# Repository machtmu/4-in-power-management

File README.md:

# 4 Inch Power Management Subsystem
I'm not gonna lie, this was a beast  

As part of the SPRINT ecosystem with MACH, this board was deisgned in the span of 5 days (From architecture to schematic to layout to production). These were not a good 5 days   

## Functionality
4 Cell BMS with high side protection FETs, integrated NVDC charging for up to 5A @ battery voltage, 3 power rails, 5V, 3.3V @ ~3A, 24V @1.8A (Shoutout Tristan)   
BMS supports up to ~5.7A due to the FET's, but if re speced, could probably go higher   
XT30's as output for 24V, input for charger and input for battery   
JST XH as input for cell balacing   
 Low side current sensing for OCP detection (or wtv else you need current for)  
 ## TODO:  
 I should change that load resistor but lowkey too tired rn :wilted_rose:   
 Order it lmao  
# Authors:  
 Architecture: javezki  
 BMS, 5V 3.3V: javezki  
 Charger, 24V Boost: kayessi 
 Layout: javezki
---

<div align="center">
  <div>

    <p><em>3D Render</em></p>
  </div>
  <br>

  <div>
    <br>
    <p><em>Schematic</em></p>
  </div>
  <br>
  
  <div>
    
    <br>
    <em>Footprint</em>
  </div>
</div>

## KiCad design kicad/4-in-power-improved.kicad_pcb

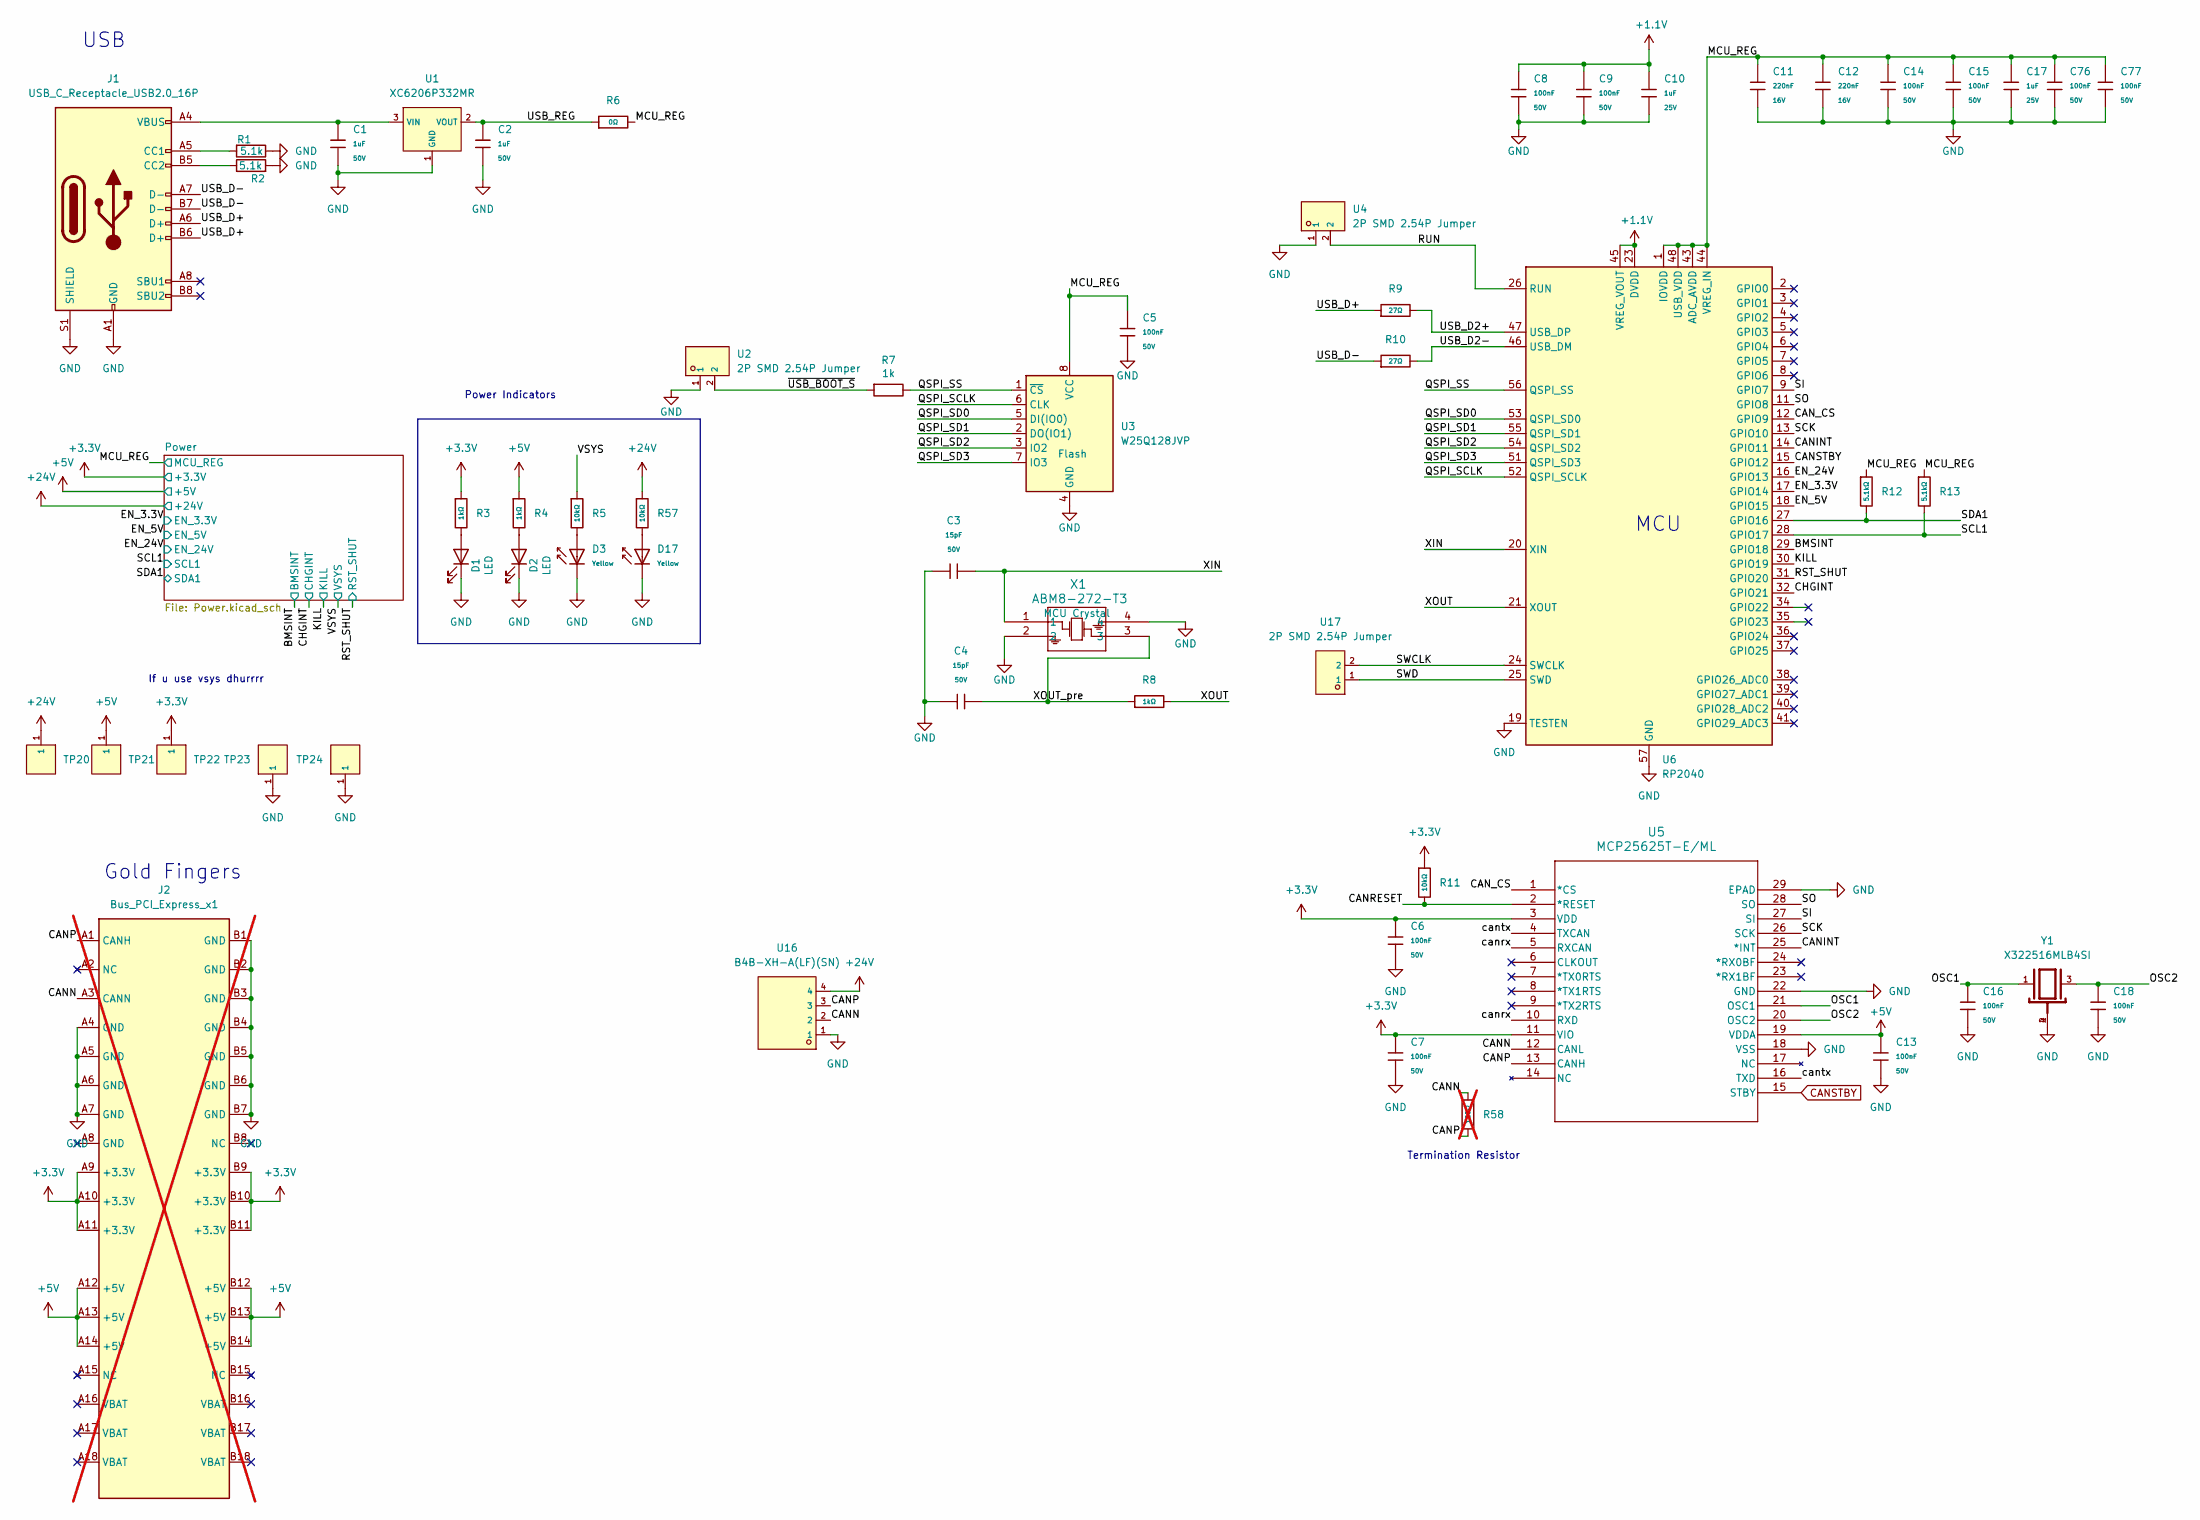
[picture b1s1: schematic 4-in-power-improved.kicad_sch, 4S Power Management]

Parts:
C1, C2: 1uF; C_0603; Voltage Rated 50V; Tolerance ±10%; Part CL10A105KB8NNNC; LCSC C15849
C3, C4: 15pF; C_0402; Voltage Rated 50V; Tolerance ±5%; Part 0402CG150J500NT; LCSC C1548
C5, C6, C7, C8, C9, C13, C14, C15, C16, C18, C76, C77: 100nF; C_0402; Voltage Rated 50V; Tolerance ±10%; Part CL05B104KB54PNC; LCSC C307331
C10, C17: 1uF; C_0402; Voltage Rated 25V; Tolerance ±10%; Part CL05A105KA5NQNC; LCSC C52923
C11, C12: 220nF; C_0402; Voltage Rated 16V; Tolerance ±10%; Part CL05B224KO5NNNC; LCSC C16772
D1, D2: LED; LED_0603_1608Metric; LCSC PN C2286
D3, D17: Yellow; D_0603; Forward Voltage (VF) 1.6V~2.6V; Part NCD0603Y2; LCSC C89811
J1: USB_C_Receptacle_USB2.0_16P; USB_C_Receptacle_Palconn_UTC16-G; LCSC PN C2765186
J2: Bus_PCI_Express_x1; PCIeX1; not fitted
R1, R2: 5.1k; R_0402_1005Metric; LCSC PN C25905
R3, R4, R8: 1kΩ; R_0402; Overload Voltage (Max) 50V; Tolerance ±1%; Part 0402WGF1001TCE; LCSC C11702
R5, R11, R57: 10kΩ; R_0402; Overload Voltage (Max) 50V; Tolerance ±1%; Part 0402WGF1002TCE; LCSC C25744
R6: 0Ω; R_0603; Overload Voltage (Max) 75V; Tolerance ±1%; Part 0603WAF0000T5E; LCSC C21189
R7: 1k; R_0402_1005Metric; LCSC Part # C11702
R9, R10: 27Ω; R_0603; Overload Voltage (Max) 75V; Tolerance ±1%; Part 0603WAF270JT5E; LCSC C25190
R12, R13: 5.1kΩ; R_0402; Overload Voltage (Max) 50V; Tolerance ±1%; Part 0402WGF5101TCE; LCSC C25905
R58: 120Ω; R_1206; Overload Voltage (Max) 200V; Tolerance ±1%; Part 1206W4F1200T5E; LCSC C17909; not fitted
TP20, TP21, TP22, TP23, TP24: RH-5015; SMD_RH-5015; LCSC C5199798
U1: XC6206P332MR; SOT-23-3_L2.9-W1.6-P1.90-LS2.8-BR; Output Voltage 3.3V; Dropout Voltage 680mV@(100mA); Part XC6206P332MR-G; LCSC C5446
U2, U4, U17: 2P SMD 2.54P Jumper; HDR-SMD_2P-P2.54-V-M-S4.8_DZ254S-11-02-50; LCSC C17702633
U3: W25Q128JVP; WSON-8-1EP_6x5mm_P1.27mm_EP3.4x4.3mm; LCSC C190862
U5: MCP25625T-E/ML; QFN-28_L6.0-W6.0-P0.65-BL-EP3.7; LCSC Part # C191253
U6: RP2040; QFN-56-1EP_7x7mm_P0.4mm_EP3.2x3.2mm; LCSC C2040
U16: B4B-XH-A(LF)(SN); CONN-TH_B4B-XH-A-LF-SN; LCSC C144395
X1: ABM8-272-T3; CRYSTAL-SMD_4P-L3.2-W2.5-BL; LCSC Part # C20625731
Y1: X322516MLB4SI; CRYSTAL-SMD_4P-L3.2-W2.5-BL; PARTREV N/A; LCSC Part # C12668

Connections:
+1.1V: C8.1, C9.1, C10.1, U6.23 (DVDD), U6.45 (VREG_VOUT), U6.50 (DVDD)
+3.3V: C6.1, C7.1, J2.A9 (+3.3V), J2.A10 (+3.3V), J2.A11 (+3.3V), J2.B9 (+3.3V), J2.B10 (+3.3V), J2.B11 (+3.3V), R3.1, R11.1, TP22.1, U5.3 (VDD), U5.11 (VIO); also elsewhere on the board
+5V: C13.1, J2.A12 (+5V), J2.A13 (+5V), J2.A14 (+5V), J2.B12 (+5V), J2.B13 (+5V), J2.B14 (+5V), R4.1, TP21.1, U5.19 (VDDA); also elsewhere on the board
+24V: R57.1, TP20.1, U16.4; also elsewhere on the board
/BMSINT: U6.29 (GPIO18); also elsewhere on the board
/CANINT: U5.25 (*INT), U6.14 (GPIO11)
/CANN: J2.A3 (CANN), R58.1, U5.12 (CANL), U16.2
/CANP: J2.A1 (CANH), R58.2, U5.13 (CANH), U16.3
/CANRESET: R11.2, U5.2 (*RESET)
/CAN_CS: U5.1 (*CS), U6.12 (GPIO9)
/CHGINT: U6.32 (GPIO21); also elsewhere on the board
/EN_3.3V: U6.17 (GPIO14); also elsewhere on the board
/EN_5V: U6.18 (GPIO15); also elsewhere on the board
/EN_24V: U6.16 (GPIO13); also elsewhere on the board
/KILL: U6.30 (GPIO19); also elsewhere on the board
/MCU_REG: C5.1, C11.1, C12.1, C14.1, C15.1, C17.1, C76.1, C77.1, R6.2, R12.1, R13.1, U3.8 (VCC), U6.1 (IOVDD), U6.10 (IOVDD), U6.22 (IOVDD), U6.33 (IOVDD), U6.42 (IOVDD), U6.43 (ADC_AVDD), U6.44 (VREG_IN), U6.48 (USB_VDD), U6.49 (IOVDD); also elsewhere on the board
/OSC1: C16.1, U5.21 (OSC1), Y1.1
/OSC2: C18.1, U5.20 (OSC2), Y1.3
/QSPI_SCLK: U3.6 (CLK), U6.52 (QSPI_SCLK)
/QSPI_SD0: U3.5 (DI(IO0)), U6.53 (QSPI_SD0)
/QSPI_SD1: U3.2 (DO(IO1)), U6.55 (QSPI_SD1)
/QSPI_SD2: U3.3 (IO2), U6.54 (QSPI_SD2)
/QSPI_SD3: U3.7 (IO3), U6.51 (QSPI_SD3)
/QSPI_SS: R7.1, U3.1 (~CS), U6.56 (QSPI_SS)
/RST_SHUT: U6.31 (GPIO20); also elsewhere on the board
/RUN: U4.2, U6.26 (RUN)
/SCK: U5.26 (SCK), U6.13 (GPIO10)
/SCL1: R13.2, U6.28 (GPIO17); also elsewhere on the board
/SDA1: R12.2, U6.27 (GPIO16); also elsewhere on the board
/SI: U5.27 (SI), U6.9 (GPIO7)
/SO: U5.28 (SO), U6.11 (GPIO8)
/SWCLK: U6.24 (SWCLK), U17.2
/SWD: U6.25 (SWD), U17.1
/USB_D2+: R9.2, U6.47 (USB_DP)
/USB_D2-: R10.2, U6.46 (USB_DM)
/USB_D+: J1.A6 (D+), J1.B6 (D+), R9.1
/USB_D-: J1.A7 (D-), J1.B7 (D-), R10.1
/USB_REG: C2.1, R6.1, U1.2 (VOUT)
/VSYS: R5.1; also elsewhere on the board
/XIN: C3.2, U6.20 (XIN), X1.1
/XOUT: R8.2, U6.21 (XOUT)
/XOUT_pre: C4.2, R8.1, X1.3
/canrx: U5.5 (RXCAN), U5.10 (RXD)
/cantx: U5.4 (TXCAN), U5.16 (TXD)
/~USB_BOOT_S: R7.2, U2.2
CANSTBY: U5.15 (STBY), U6.15 (GPIO12)
GND: C1.2, C2.2, C3.1, C4.1, C5.2, C6.2, C7.2, C8.2, C9.2, C10.2, C11.2, C12.2, C13.2, C14.2, C15.2, C16.2, C17.2, C18.2, C76.2, C77.2, D1.1 (K), D2.1 (K), D3.1, D17.1, J1.A1 (GND), J1.A12 (GND), J1.B1 (GND), J1.B12 (GND), J1.S1 (SHIELD), J2.A4 (GND), J2.A5 (GND), J2.A6 (GND), J2.A7 (GND), J2.B1 (GND), J2.B2 (GND), J2.B3 (GND), J2.B4 (GND), J2.B5 (GND), J2.B6 (GND), J2.B7 (GND), R1.1, R2.2, TP23.1, TP24.1, U1.1 (GND), U2.1, U3.4 (GND), U4.1, U5.18 (VSS), U5.22 (GND), U5.29 (EPAD), U6.19 (TESTEN), U6.57 (GND), U16.1, X1.2, X1.4, Y1.2, Y1.4; also elsewhere on the board
unnamed: D1.2 (A), R3.2
unnamed: D2.2 (A), R4.2
unnamed: D3.2, R5.2
unnamed: D17.2, R57.2
unnamed: J1.A5 (CC1), R1.2
unnamed: J1.B5 (CC2), R2.1
unnamed: C1.1, J1.A4 (VBUS), J1.A9 (VBUS), J1.B4 (VBUS), J1.B9 (VBUS), U1.3 (VIN)

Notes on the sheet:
USB
MCU
Power Indicators
Termination Resistor
If u use vsys dhurrrr
Gold Fingers

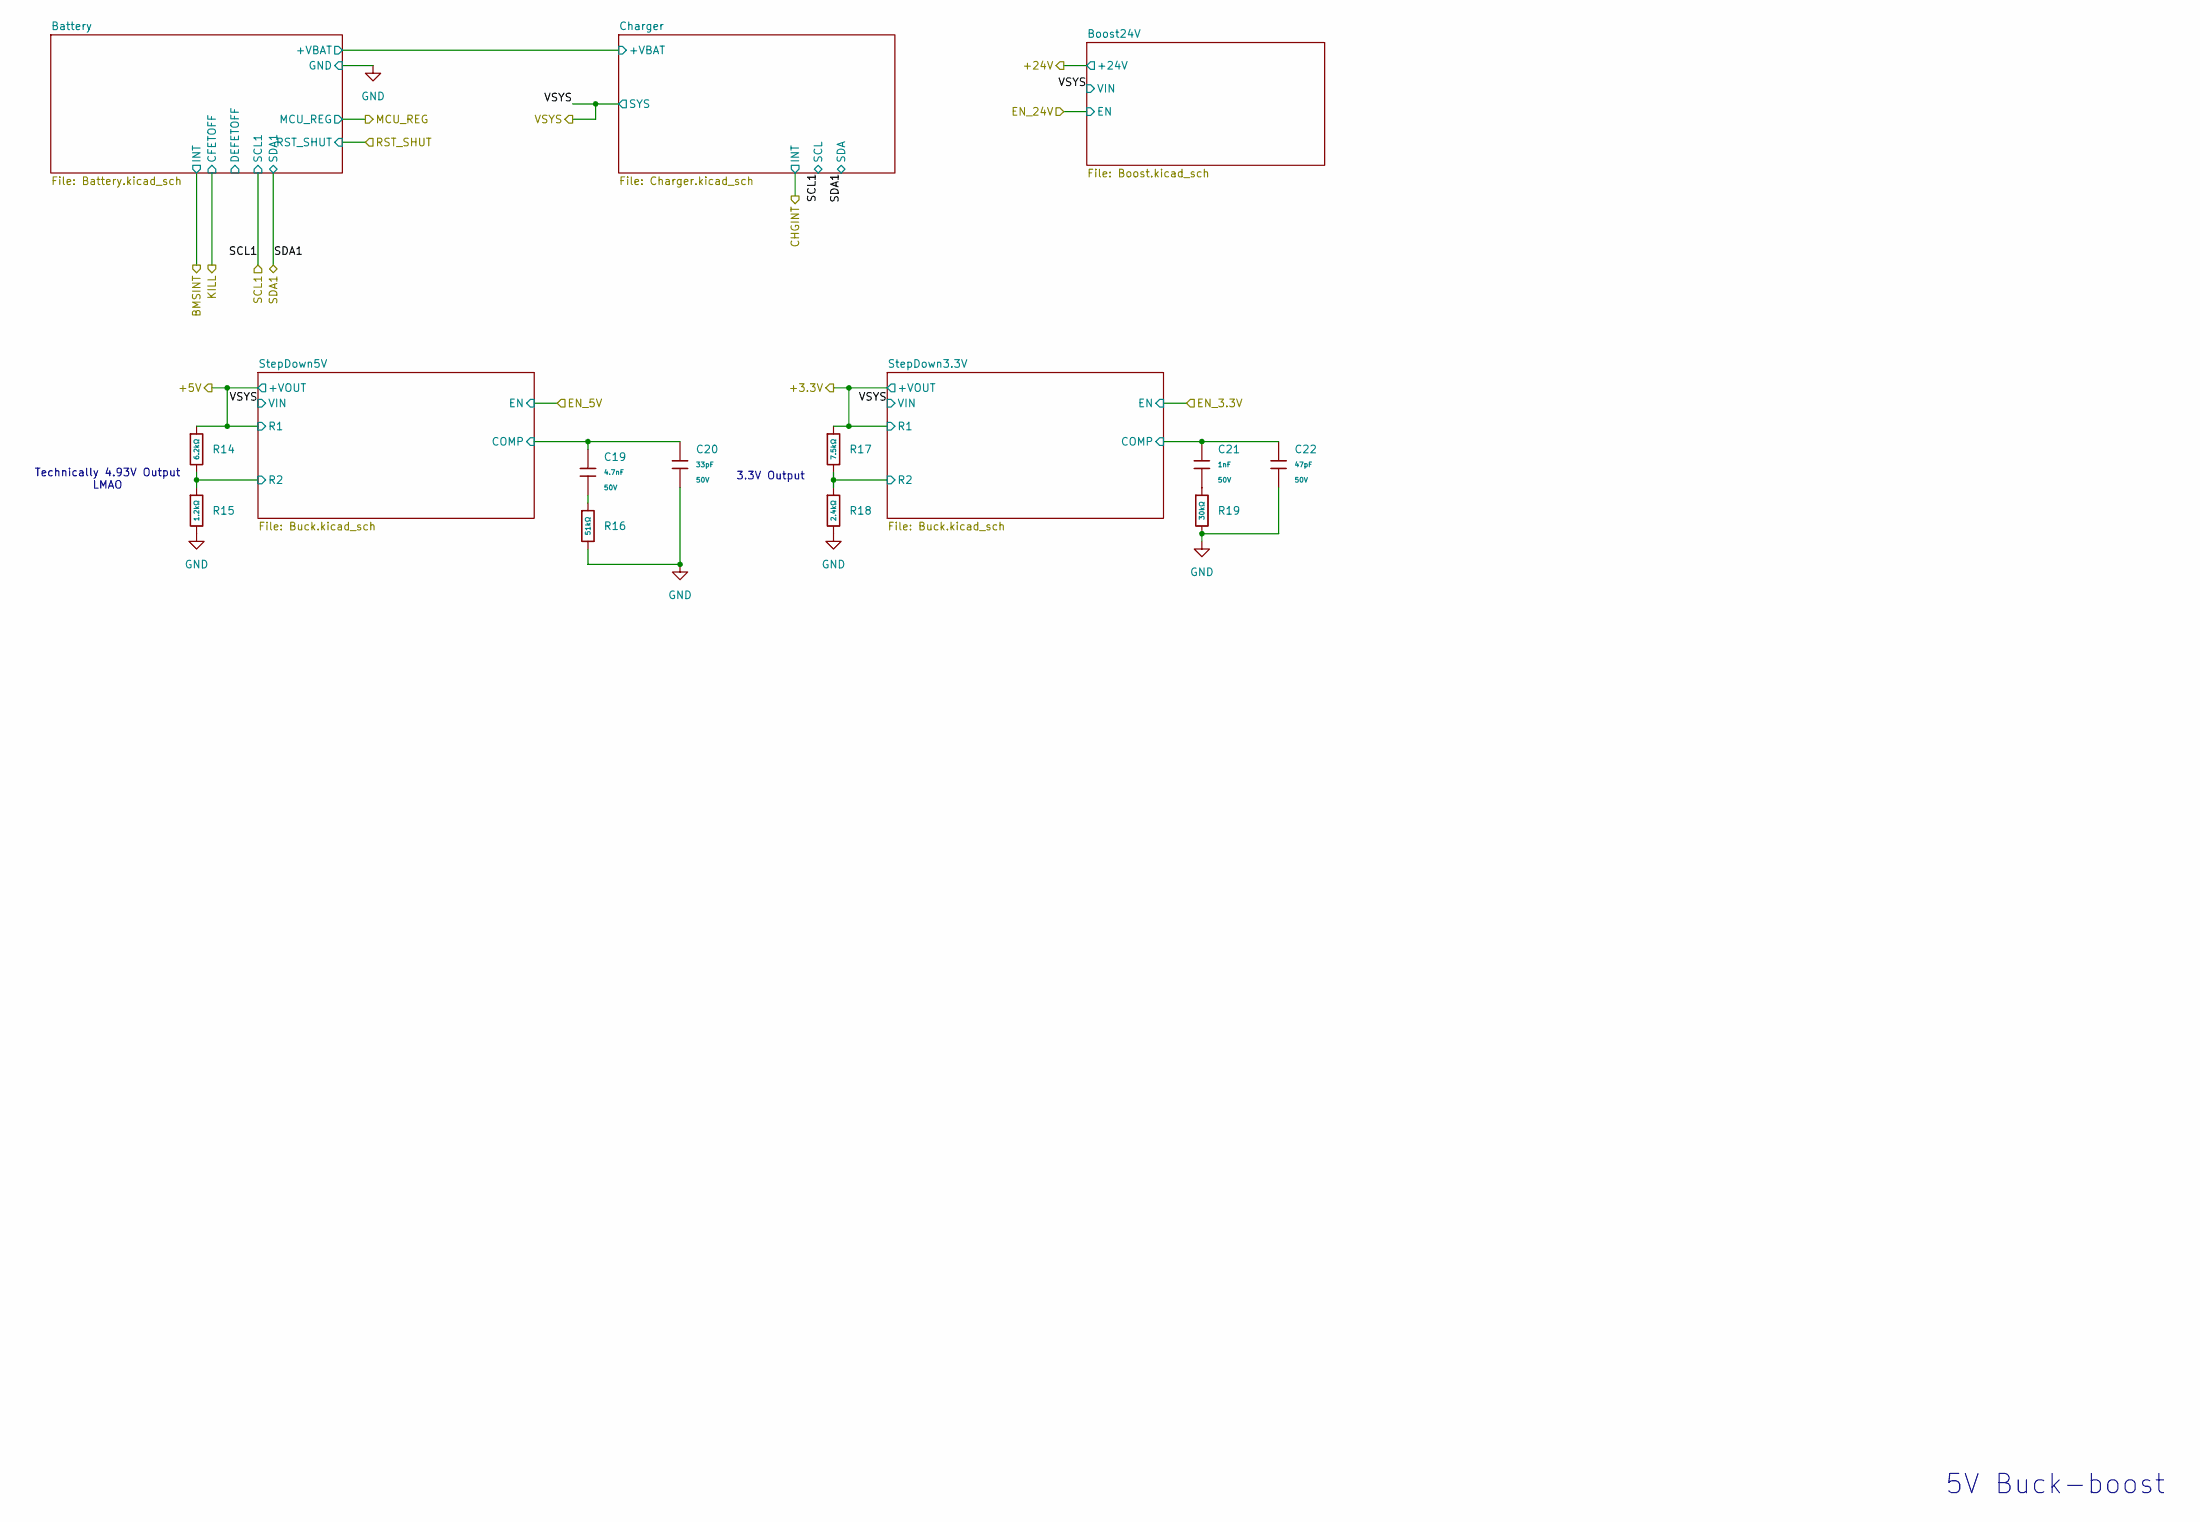
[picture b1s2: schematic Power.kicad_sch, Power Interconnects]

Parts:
C19: 4.7nF; C_0402; Voltage Rated 50V; Tolerance ±10%; Part 0402B472K500NT; LCSC C1538
C20: 33pF; C_0805; Voltage Rated 50V; Tolerance ±5%; Part CC0805JRNPO9BN330; LCSC C107115
C21: 1nF; C_0402; Voltage Rated 50V; Tolerance ±10%; Part 0402B102K500NT; LCSC C1523
C22: 47pF; C_0402; Voltage Rated 50V; Tolerance ±5%; Part 0402CG470J500NT; LCSC C1567
R14: 6.2kΩ; R_0805; Overload Voltage (Max) 150V; Tolerance ±1%; Part 0805W8F6201T5E; LCSC C17767
R15: 1.2kΩ; R_0805; Overload Voltage (Max) 150V; Tolerance ±1%; Part 0805W8F1201T5E; LCSC C17379
R16: 51kΩ; R_0805; Overload Voltage (Max) 150V; Tolerance ±1%; Part 0805W8F5102T5E; LCSC C17737
R17: 7.5kΩ; R_0402; Overload Voltage (Max) 50V; Tolerance ±1%; Part 0402WGF7501TCE; LCSC C25918
R18: 2.4kΩ; R_0402; Overload Voltage (Max) 50V; Tolerance ±1%; Part 0402WGF2401TCE; LCSC C25882
R19: 30kΩ; R_0603; Overload Voltage (Max) 75V; Tolerance ±1%; Part 0603WAF3002T5E; LCSC C22984

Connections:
+3.3V: R17.1; also elsewhere on the board
+5V: R14.1; also elsewhere on the board
/Power/StepDown3.3V/COMP: C21.1, C22.1; also elsewhere on the board
/Power/StepDown3.3V/R2: R17.2, R18.1; also elsewhere on the board
/Power/StepDown5V/COMP: C19.1, C20.1; also elsewhere on the board
/Power/StepDown5V/R2: R14.2, R15.1; also elsewhere on the board
GND: C20.2, C22.2, R15.2, R16.2, R18.2, R19.2; also elsewhere on the board
unnamed: C19.2, R16.1
unnamed: C21.2, R19.1

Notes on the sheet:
Technically 4.93V Output LMAO
5V Buck-boost
3.3V Output

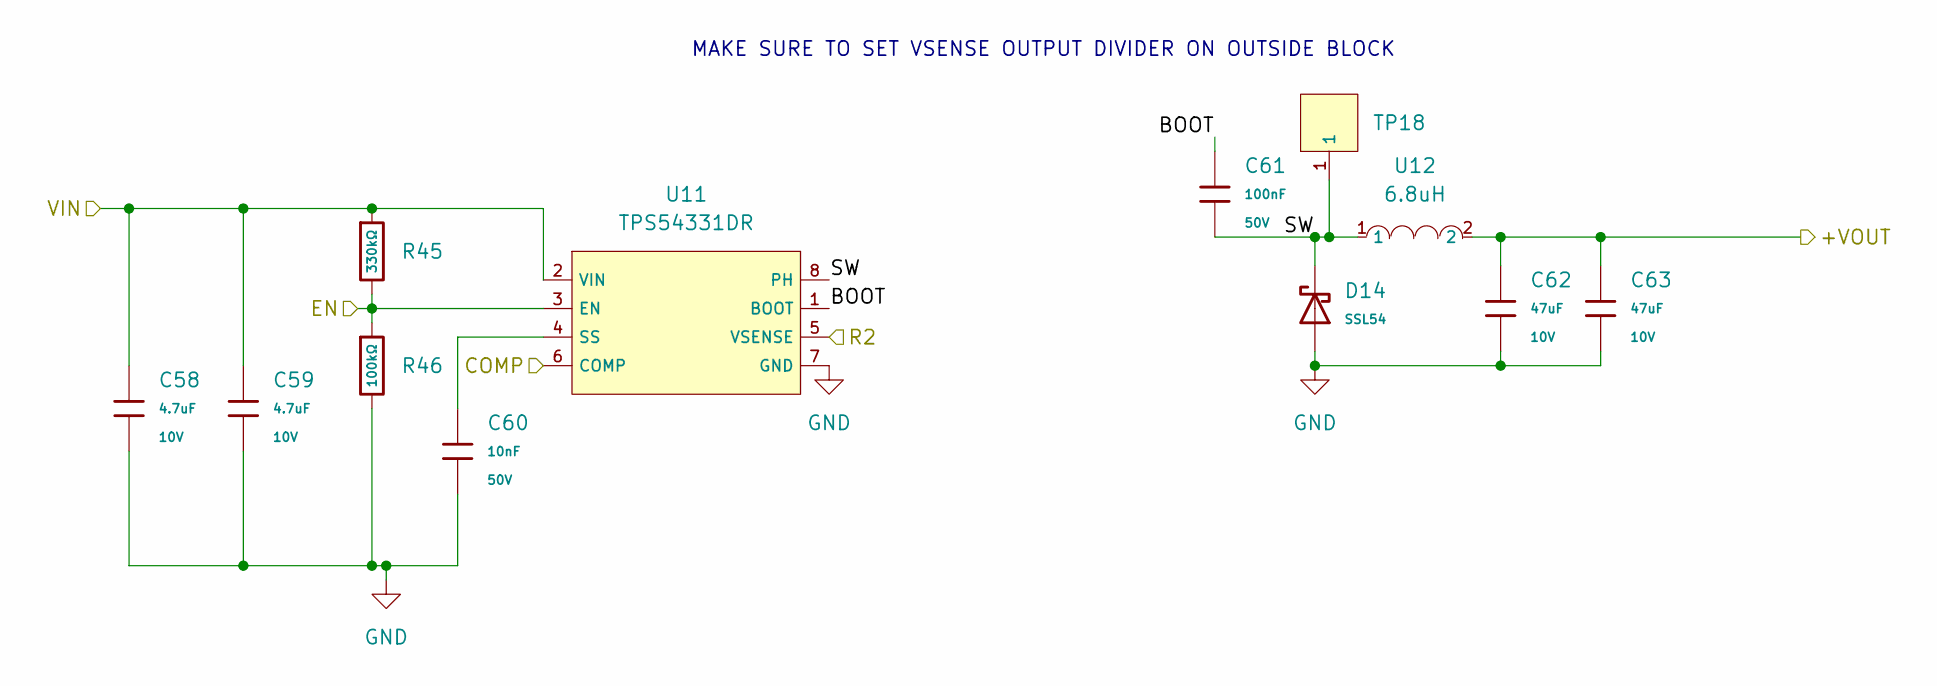
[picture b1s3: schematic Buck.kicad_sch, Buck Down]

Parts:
C58, C59: 4.7uF; C_0402; Voltage Rated 10V; Tolerance ±20%; Part CL05A475MP5NRNC; LCSC C23733
C60: 10nF; C_0402; Voltage Rated 50V; Tolerance ±10%; Part CL05B103KB5NNNC; LCSC C15195
C61: 100nF; C_0402; Voltage Rated 50V; Tolerance ±10%; Part CL05B104KB54PNC; LCSC C307331
C62, C63: 47uF; C_1206; Voltage Rated 10V; Tolerance ±20%; Part CL31A476MPHNNNE; LCSC C96123
D14: SSL54; D_SMA; Forward Voltage (Vf@If) 480mV@5A; Reverse Voltage (Vr) 40V; Part SSL54; LCSC C41410770
R45: 330kΩ; R_0805; Overload Voltage (Max) 150V; Tolerance ±1%; Part 0805W8F3303T5E; LCSC C17629
R46: 100kΩ; R_0805; Overload Voltage (Max) 150V; Tolerance ±1%; Part 0805W8F1003T5E; LCSC C149504
TP18: RH-5015; SMD_RH-5015; LCSC C5199798
U11: TPS54331DR; SOIC-8_L5.0-W4.0-P1.27-LS6.0-BL; Output Voltage 0.8V~25V; Input Voltage 3.5V~28V; Part TPS54331DR; LCSC C9865
U12: 6.8uH; IND-SMD_L5.4-W5.2_SLO0530H6R8MTT; MFR PART# SLO0530H6R8MTT; LCSC C325965

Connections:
+5V: C62.1, C63.1, U12.2; also elsewhere on the board
/EN_5V: R45.2, R46.1, U11.3 (EN); also elsewhere on the board
/Power/StepDown5V/BOOT: C61.1, U11.1 (BOOT)
/Power/StepDown5V/COMP: U11.6 (COMP); also elsewhere on the board
/Power/StepDown5V/R2: U11.5 (VSENSE); also elsewhere on the board
/Power/StepDown5V/SW: C61.2, D14.1, TP18.1, U11.8 (PH), U12.1
/VSYS: C58.1, C59.1, R45.1, U11.2 (VIN); also elsewhere on the board
GND: C58.2, C59.2, C60.2, C62.2, C63.2, D14.2, R46.2, U11.7 (GND); also elsewhere on the board
unnamed: C60.1, U11.4 (SS)

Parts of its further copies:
C64, C65: 4.7uF; C_0402; Voltage Rated 10V; Tolerance ±20%; Part CL05A475MP5NRNC; LCSC C23733
C66: 10nF; C_0402; Voltage Rated 50V; Tolerance ±10%; Part CL05B103KB5NNNC; LCSC C15195
C67: 100nF; C_0402; Voltage Rated 50V; Tolerance ±10%; Part CL05B104KB54PNC; LCSC C307331
C68, C69: 47uF; C_1206; Voltage Rated 10V; Tolerance ±20%; Part CL31A476MPHNNNE; LCSC C96123
D15: SSL54; D_SMA; Forward Voltage (Vf@If) 480mV@5A; Reverse Voltage (Vr) 40V; Part SSL54; LCSC C41410770
R47: 330kΩ; R_0805; Overload Voltage (Max) 150V; Tolerance ±1%; Part 0805W8F3303T5E; LCSC C17629
R48: 100kΩ; R_0805; Overload Voltage (Max) 150V; Tolerance ±1%; Part 0805W8F1003T5E; LCSC C149504
TP19: RH-5015; SMD_RH-5015; LCSC C5199798
U13: TPS54331DR; SOIC-8_L5.0-W4.0-P1.27-LS6.0-BL; Output Voltage 0.8V~25V; Input Voltage 3.5V~28V; Part TPS54331DR; LCSC C9865
U14: 6.8uH; IND-SMD_L5.4-W5.2_SLO0530H6R8MTT; MFR PART# SLO0530H6R8MTT; LCSC C325965

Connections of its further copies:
+3.3V: C68.1, C69.1, U14.2; also elsewhere on the board
/EN_3.3V: R47.2, R48.1, U13.3 (EN); also elsewhere on the board
/Power/StepDown3.3V/BOOT: C67.1, U13.1 (BOOT)
/Power/StepDown3.3V/COMP: U13.6 (COMP); also elsewhere on the board
/Power/StepDown3.3V/R2: U13.5 (VSENSE); also elsewhere on the board
/Power/StepDown3.3V/SW: C67.2, D15.1, TP19.1, U13.8 (PH), U14.1
/VSYS: C64.1, C65.1, R47.1, U13.2 (VIN); also elsewhere on the board
GND: C64.2, C65.2, C66.2, C68.2, C69.2, D15.2, R48.2, U13.7 (GND); also elsewhere on the board
unnamed: C66.1, U13.4 (SS)

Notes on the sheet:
MAKE SURE TO SET VSENSE OUTPUT DIVIDER ON OUTSIDE BLOCK

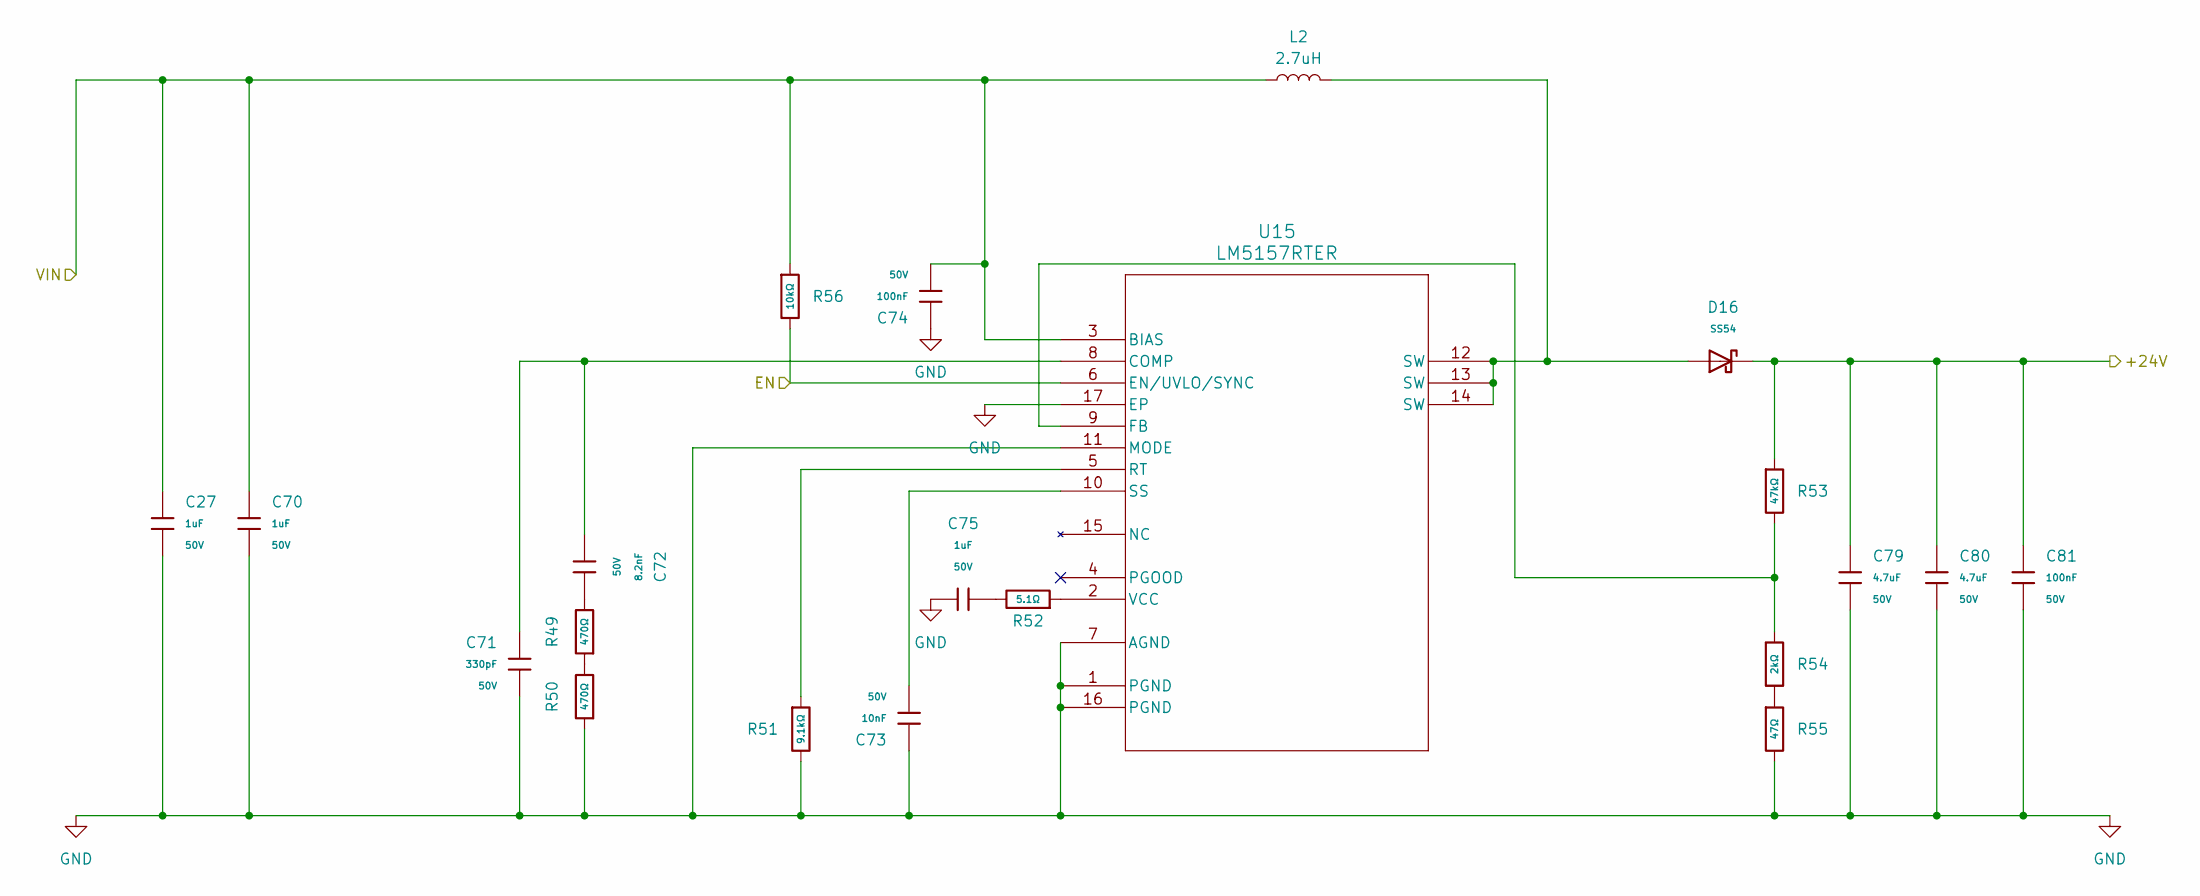
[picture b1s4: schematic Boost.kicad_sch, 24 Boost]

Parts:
C27, C70: 1uF; C_0805; Voltage Rated 50V; Tolerance ±10%; Part CL21B105KBFNNNE; LCSC C28323
C71: 330pF; C_0603; Voltage Rated 50V; Tolerance ±5%; Part CL10C331JB8NNNC; LCSC C1664
C72: 8.2nF; C_0603; Voltage Rated 50V; Tolerance ±10%; Part 0603B822K500NT; LCSC C1322360
C73: 10nF; C_0402; Voltage Rated 50V; Tolerance ±10%; Part CL05B103KB5NNNC; LCSC C15195
C74, C81: 100nF; C_0402; Voltage Rated 50V; Tolerance ±10%; Part CL05B104KB54PNC; LCSC C307331
C75: 1uF; C_0603; Voltage Rated 50V; Tolerance ±10%; Part CL10A105KB8NNNC; LCSC C15849
C79, C80: 4.7uF; C_1206; Voltage Rated 50V; Tolerance ±10%; Part 1206B475K500NT; LCSC C29823
D16: SS54; D_SMA; Forward Voltage (Vf@If) 550mV@5A; Reverse Voltage (Vr) 40V; Part SS54; LCSC C22452
L2: 2.7uH; IND-SMD_L7.5-W7.5_XAL7030; LCSC C5366402
R49, R50: 470Ω; R_0603; Overload Voltage (Max) 75V; Tolerance ±1%; Part 0603WAF4700T5E; LCSC C23179
R51: 9.1kΩ; R_0603; Overload Voltage (Max) 75V; Tolerance ±1%; Part 0603WAF9101T5E; LCSC C23260
R52: 5.1Ω; R_0603; Overload Voltage (Max) 75V; Tolerance ±1%; Part 0603WAF510KT5E; LCSC C25197
R53: 47kΩ; R_0402; Overload Voltage (Max) 50V; Tolerance ±1%; Part 0402WGF4702TCE; LCSC C25792
R54: 2kΩ; R_0402; Overload Voltage (Max) 50V; Tolerance ±1%; Part 0402WGF2001TCE; LCSC C4109
R55: 47Ω; R_0402; Overload Voltage (Max) 50V; Tolerance ±1%; Part 0402WGF470JTCE; LCSC C25118
R56: 10kΩ; R_0402; Overload Voltage (Max) 50V; Tolerance ±1%; Part 0402WGF1002TCE; LCSC C25744
U15: LM5157RTER; WQFN-16_L3.0-W3.0-P0.50-TL-EP1.7; LCSC C5219222

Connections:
+24V: C79.1, C80.1, C81.1, D16.1, R53.1; also elsewhere on the board
/EN_24V: R56.2, U15.6 (EN/UVLO/SYNC); also elsewhere on the board
/VSYS: C27.1, C70.1, C74.1, L2.1, R56.1, U15.3 (BIAS); also elsewhere on the board
GND: C27.2, C70.2, C71.1, C73.1, C74.2, C75.2, C79.2, C80.2, C81.2, R50.1, R51.2, R55.2, U15.1 (PGND), U15.7 (AGND), U15.11 (MODE), U15.16 (PGND), U15.17 (EP); also elsewhere on the board
unnamed: C72.2, R49.2
unnamed: C75.1, R52.2
unnamed: D16.2, L2.2, U15.12 (SW), U15.13 (SW), U15.14 (SW)
unnamed: R49.1, R50.2
unnamed: R54.2, R55.1
unnamed: C71.2, C72.1, U15.8 (COMP)
unnamed: R53.2, R54.1, U15.9 (FB)
unnamed: R51.1, U15.5 (RT)
unnamed: C73.2, U15.10 (SS)
unnamed: R52.1, U15.2 (VCC)

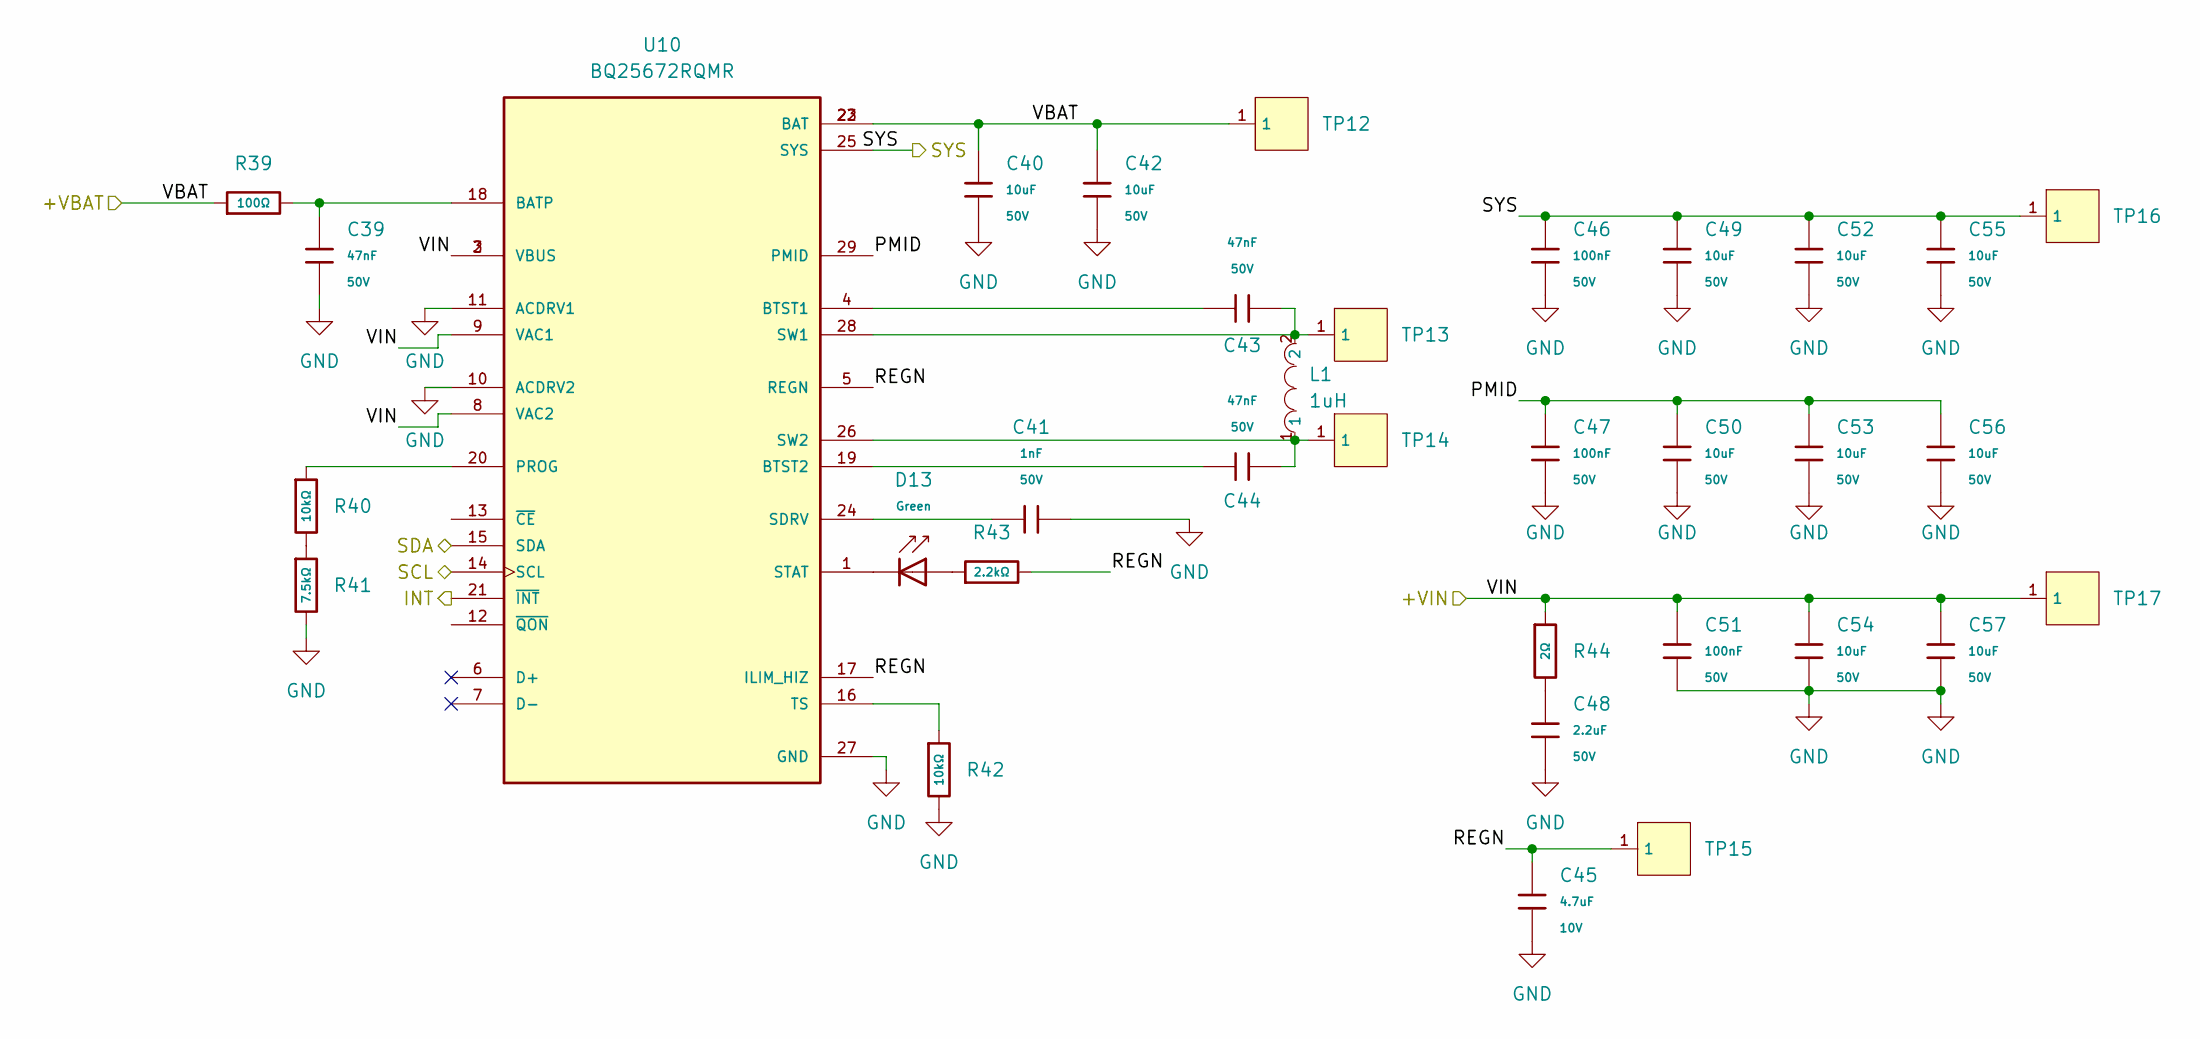
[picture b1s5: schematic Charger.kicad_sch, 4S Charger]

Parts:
C39, C43, C44: 47nF; C_0603; Voltage Rated 50V; Tolerance ±10%; Part CL10B473KB8NNNC; LCSC C1622
C40, C42, C49, C50, C52, C53, C54, C55, C56, C57: 10uF; C_0805; Voltage Rated 50V; Tolerance ±10%; Part GRM21BR61H106KE43L; LCSC C440198
C41: 1nF; C_0402; Voltage Rated 50V; Tolerance ±10%; Part 0402B102K500NT; LCSC C1523
C45: 4.7uF; C_0402; Voltage Rated 10V; Tolerance ±20%; Part CL05A475MP5NRNC; LCSC C23733
C46, C47, C51: 100nF; C_0402; Voltage Rated 50V; Tolerance ±10%; Part CL05B104KB54PNC; LCSC C307331
C48: 2.2uF; C_0805; Voltage Rated 50V; Tolerance ±10%; Part CL21A225KBQNNNE; LCSC C377773
D13: Green; D_0805; Part KT-0805G; LCSC C2297
L1: 1uH; IND-SMD_L3.2-W2.5-1; LCSC C5159968
R39: 100Ω; R_0402; Overload Voltage (Max) 50V; Tolerance ±1%; Part 0402WGF1000TCE; LCSC C25076
R40, R42: 10kΩ; R_0402; Overload Voltage (Max) 50V; Tolerance ±1%; Part 0402WGF1002TCE; LCSC C25744
R41: 7.5kΩ; R_0402; Overload Voltage (Max) 50V; Tolerance ±1%; Part 0402WGF7501TCE; LCSC C25918
R43: 2.2kΩ; R_0402; Overload Voltage (Max) 50V; Tolerance ±1%; Part 0402WGF2201TCE; LCSC C25879
R44: 2Ω; R_0603; Overload Voltage (Max) 75V; Tolerance ±1%; Part 0603WAF200KT5E; LCSC C22977
TP12, TP13, TP14, TP15, TP16, TP17: RH-5015; SMD_RH-5015; LCSC C5199798
U10: BQ25672RQMR; IC_BQ25672RQMR; PARTREV A

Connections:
/CHGINT: U10.21 (~INT); also elsewhere on the board
/Power/Battery/PACK+: C40.1, C42.1, R39.1, TP12.1, U10.22 (BAT), U10.23 (BAT); also elsewhere on the board
/Power/Charger/PMID: C47.1, C50.1, C53.1, C56.1, U10.29 (PMID)
/Power/Charger/REGN: C45.1, R43.2, TP15.1, U10.5 (REGN), U10.17 (ILIM_HIZ)
/Power/Charger/VIN: C51.1, C54.1, C57.1, R44.1, TP17.1, U10.2 (VBUS), U10.3 (VBUS), U10.8 (VAC2), U10.9 (VAC1)
/SCL1: U10.14 (SCL); also elsewhere on the board
/SDA1: U10.15 (SDA); also elsewhere on the board
/VSYS: C46.1, C49.1, C52.1, C55.1, TP16.1, U10.25 (SYS); also elsewhere on the board
GND: C39.2, C40.2, C41.2, C42.2, C45.2, C46.2, C47.2, C48.2, C49.2, C50.2, C51.2, C52.2, C53.2, C54.2, C55.2, C56.2, C57.2, R41.2, R42.2, U10.10 (ACDRV2), U10.11 (ACDRV1), U10.27 (GND); also elsewhere on the board
unnamed: C48.1, R44.2
unnamed: D13.2, R43.1
unnamed: R40.2, R41.1
unnamed: C39.1, R39.2, U10.18 (BATP)
unnamed: C43.1, U10.4 (BTST1)
unnamed: C44.1, U10.19 (BTST2)
unnamed: R40.1, U10.20 (PROG)
unnamed: C41.1, U10.24 (SDRV)
unnamed: D13.1, U10.1 (STAT)
unnamed: C43.2, L1.2, TP13.1, U10.28 (SW1)
unnamed: C44.2, L1.1, TP14.1, U10.26 (SW2)
unnamed: R42.1, U10.16 (TS)
